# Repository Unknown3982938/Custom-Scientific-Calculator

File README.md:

# Custom-Scientific-Calculator
An open-source custom scientific calculator based on an ESP32, featuring a dedicated keypad matrix, MCP23017 I/O expansion, ST7789 display, rechargeable Li-ion power system, and a custom PCB.

# Project Status
## Work-In-Progress (WIP)
The hardware is currently undergoing PCB and mechanical development. Firmware and enclosure designs are also under active development and may change as physical prototypes are assembled and tested.

# Features
- ESP32-based controller
- ST7789 Color TFT (2.8 inch)
- MCP23017 I/O Expander
- 45 key Physical key matrix (custom)
- SD card support(OPTIONAL)
- Scientific and mathematical functions
- Rechargeable battery
- Modular/Serviceable design (planned to make a compact version, consisting of SMTs instead of THTs)
- Custom PCB
- Custom enclosure

# Repository Contents
- HARDWARE/ - Schematic, BOM, and PCB layout
- FIRMWARE/ - Sketch Code and other software related contents
- CAD/ENCLOSURE/ - Enclosure and Mechanical CAD files
- Manufacturing/ - fabrication-ready manufacturing files
- REFERENCES - Additional materials and information (e.g. Simulations, tests, and additional datas)

# Hardware
The calculator uses a custom PCB designed specifically for the project. The hardware is still being refined and has not yet completed final physical validation.

# Firmware
Firmware development is currently in progress. The included firmware represents the current development state and is subject to change as the hardware is validated.

# CAD
The enclosure and other mechanical components are included as CAD files. These designs are still being refined alongside the PCB and physical prototype.

# Goals
The goal is to create a functional, portable scientific calculator while gaining practical experience in:
- PCB design
- Embedded programming
- Human-machine interfaces
- Power management
- Mechanical design
- Electronics Manufacturing

---

The project is being developed incrementally, with hardware and software tested as each subsystem is completed.

---

# Socials:
(for other projects that is currently independently developed)

- https://tiktok.com/@philie_imation_001 (TIKTOK account)
- (some are set to private for now)

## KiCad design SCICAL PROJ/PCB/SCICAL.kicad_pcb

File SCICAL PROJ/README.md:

# Custom-Scientific-Calculator
A custom-built scientific calculator designed and developed from scratch as a hardware project.

# Features
- ESP32 Based man controller
- Color TFT (2.8 inch)
- Physical key matrix (custom)
- Scientific and mathematical functions
- Rechargeable battery 
- Custom PCB
- Custom enclosure

# Project status
The project is currently in development. The schematic and PCB are being designed, while the firmware and user interface are being developed alongsde the hardware

# Goals
The goal is to create a functional, portable scientific calculator while gaining practical experience in:
- PCB design
- Embedded programmng
- Human-machine interfaces
- Power management
- Mechanical design
- Electronics Manufucturing

---

The project is being developed incrementally, with hardware and software tested as each subsystem is completed.

---

# Code:
(Currently still on queue, it will be set into development once hardware is acquired and finished)

---

# Socials:
(for other projects that is currently independently developed)

- https://tiktok.com/@philie_imation_001 (TIKTOK account)
- (some are set to private for now)

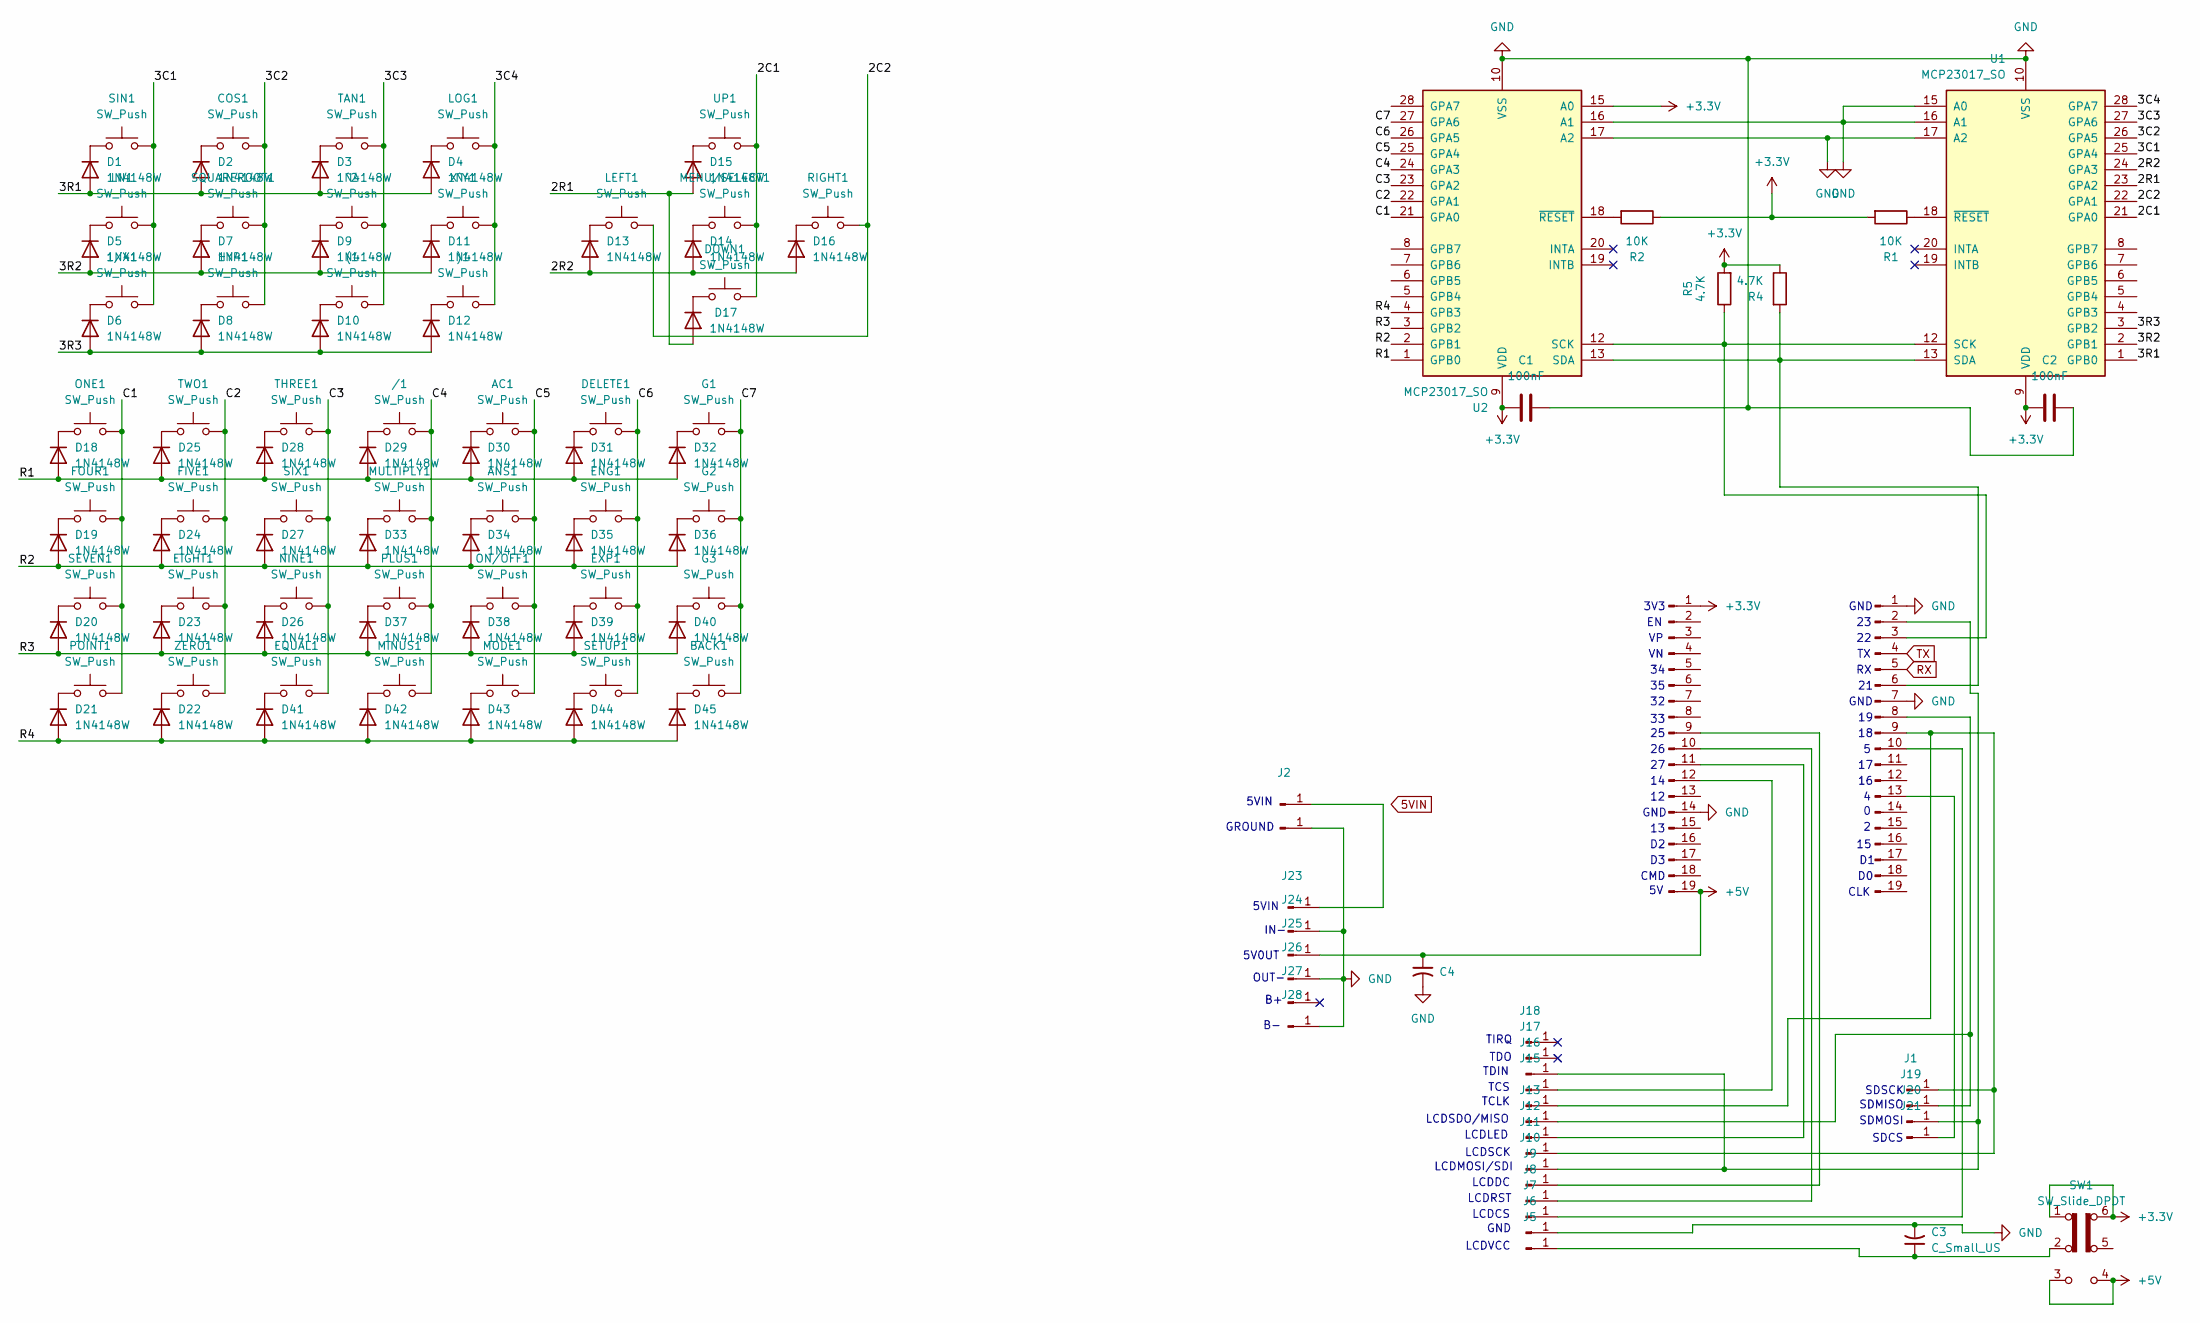
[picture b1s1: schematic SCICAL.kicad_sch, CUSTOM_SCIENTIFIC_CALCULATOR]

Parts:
1/X1: SW_Push; SW_PUSH_6mm
(1: SW_Push; SW_PUSH_6mm
)1: SW_Push; SW_PUSH_6mm
/1: SW_Push; SW_PUSH_6mm
AC1: SW_Push; SW_PUSH_6mm
ANS1: SW_Push; SW_PUSH_6mm
BACK1: SW_Push; SW_PUSH_6mm
C1, C2: 100nF; C_Disc_D3.0mm_W1.6mm_P2.50mm
C3: C_Small_US; C_Radial_D4.0mm_H5.0mm_P1.50mm
C4: C_Small_US; C_Radial_D5.0mm_H11.0mm_P2.00mm
COS1: SW_Push; SW_PUSH_6mm
D1, D2, D3, D4, D5, D6, D7, D8, D9, D10, D11, D12, D13, D14, D15, D16, D17, D18, D19, D20, D21, D22, D23, D24, D25, D26, D27, D28, D29, D30, D31, D32, D33, D34, D35, D36, D37, D38, D39, D40, D41, D42, D43, D44, D45: 1N4148W; D_DO-35_SOD27_P7.62mm_Horizontal
DELETE1: SW_Push; SW_PUSH_6mm
DOWN1: SW_Push; SW_PUSH_6mm
EIGHT1: SW_Push; SW_PUSH_6mm
ENG1: SW_Push; SW_PUSH_6mm
EQUAL1: SW_Push; SW_PUSH_6mm
EXP1: SW_Push; SW_PUSH_6mm
FIVE1: SW_Push; SW_PUSH_6mm
FOUR1: SW_Push; SW_PUSH_6mm
G1, G2, G3: SW_Push; SW_PUSH_6mm
HYP1: SW_Push; SW_PUSH_6mm
J1, J2, J5, J6, J7, J8, J9, J10, J11, J12, J13, J14, J15, J16, J17, J18, J19, J20, J21, J22: Conn_01x01_Pin; SolderWirePad_1x01_SMD_1x2mm
J3, J4: Conn_01x19_Pin; PinHeader_1x19_P2.54mm_Vertical
J23, J24, J25, J26, J27, J28: Conn_01x01_Pin; TestPoint_Pad_2.0x2.0mm
LEFT1: SW_Push; SW_PUSH_6mm
LN1: SW_Push; SW_PUSH_6mm
LOG1: SW_Push; SW_PUSH_6mm
MENU/SELECT1: SW_Push; SW_PUSH_6mm
MINUS1: SW_Push; SW_PUSH_6mm
MODE1: SW_Push; SW_PUSH_6mm
MULTIPLY1: SW_Push; SW_PUSH_6mm
NINE1: SW_Push; SW_PUSH_6mm
ON/OFF1: SW_Push; SW_PUSH_6mm
ONE1: SW_Push; SW_PUSH_6mm
PLUS1: SW_Push; SW_PUSH_6mm
POINT1: SW_Push; SW_PUSH_6mm
R1, R2: 10K; R_Axial_DIN0207_L6.3mm_D2.5mm_P10.16mm_Horizontal
R4, R5: 4.7K; R_Axial_DIN0207_L6.3mm_D2.5mm_P10.16mm_Horizontal
RIGHT1: SW_Push; SW_PUSH_6mm
SETUP1: SW_Push; SW_PUSH_6mm
SEVEN1: SW_Push; SW_PUSH_6mm
SIN1: SW_Push; SW_PUSH_6mm
SIX1: SW_Push; SW_PUSH_6mm
SQUAREROOT1: SW_Push; SW_PUSH_6mm
SW1: SW_Slide_DPDT; SW_CK_JS202011CQN_DPDT_Straight
TAN1: SW_Push; SW_PUSH_6mm
THREE1: SW_Push; SW_PUSH_6mm
TWO1: SW_Push; SW_PUSH_6mm
U1, U2: MCP23017_SO; SOIC-28W_7.5x17.9mm_P1.27mm
UP1: SW_Push; SW_PUSH_6mm
X^Y1: SW_Push; SW_PUSH_6mm
ZERO1: SW_Push; SW_PUSH_6mm
^2: SW_Push; SW_PUSH_6mm

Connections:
+3.3V: C1.1, C2.2, J3.1, R1.2, R2.1, R4.1, R5.2, SW1.1 (A), SW1.6 (C), U1.9 (VDD), U2.9 (VDD), U2.15 (A0)
+5V: C4.1, J3.19, J25.1, SW1.3 (C), SW1.4 (A)
/2C1: DOWN1.2, MENU/SELECT1.2, U1.21 (GPA0), UP1.2
/2C2: LEFT1.2, RIGHT1.2, U1.22 (GPA1)
/2R1: D15.2 (A), D17.2 (A), U1.23 (GPA2)
/2R2: D13.2 (A), D14.2 (A), D16.2 (A), U1.24 (GPA3)
/3C1: 1/X1.2, LN1.2, SIN1.2, U1.25 (GPA4)
/3C2: COS1.2, HYP1.2, SQUAREROOT1.2, U1.26 (GPA5)
/3C3: (1.2, TAN1.2, U1.27 (GPA6), ^2.2
/3C4: )1.2, LOG1.2, U1.28 (GPA7), X^Y1.2
/3R1: D1.2 (A), D2.2 (A), D3.2 (A), D4.2 (A), U1.1 (GPB0)
/3R2: D5.2 (A), D7.2 (A), D9.2 (A), D11.2 (A), U1.2 (GPB1)
/3R3: D6.2 (A), D8.2 (A), D10.2 (A), D12.2 (A), U1.3 (GPB2)
/C1: FOUR1.2, ONE1.2, POINT1.2, SEVEN1.2, U2.21 (GPA0)
/C2: EIGHT1.2, FIVE1.2, TWO1.2, U2.22 (GPA1), ZERO1.2
/C3: EQUAL1.2, NINE1.2, SIX1.2, THREE1.2, U2.23 (GPA2)
/C4: /1.2, MINUS1.2, MULTIPLY1.2, PLUS1.2, U2.24 (GPA3)
/C5: AC1.2, ANS1.2, MODE1.2, ON/OFF1.2, U2.25 (GPA4)
/C6: DELETE1.2, ENG1.2, EXP1.2, SETUP1.2, U2.26 (GPA5)
/C7: BACK1.2, G1.2, G2.2, G3.2, U2.27 (GPA6)
/R1: D18.2 (A), D25.2 (A), D28.2 (A), D29.2 (A), D30.2 (A), D31.2 (A), D32.2 (A), U2.1 (GPB0)
/R2: D19.2 (A), D24.2 (A), D27.2 (A), D33.2 (A), D34.2 (A), D35.2 (A), D36.2 (A), U2.2 (GPB1)
/R3: D20.2 (A), D23.2 (A), D26.2 (A), D37.2 (A), D38.2 (A), D39.2 (A), D40.2 (A), U2.3 (GPB2)
/R4: D21.2 (A), D22.2 (A), D41.2 (A), D42.2 (A), D43.2 (A), D44.2 (A), D45.2 (A), U2.4 (GPB3)
GND: C1.2, C2.1, C3.2, C4.2, J3.14, J4.1, J4.7, J6.1, J22.1, J24.1, J26.1, J28.1, U1.10 (VSS), U1.15 (A0), U1.16 (A1), U1.17 (A2), U2.10 (VSS), U2.16 (A1), U2.17 (A2)
unnamed: D1.1 (K), SIN1.1
unnamed: COS1.1, D2.1 (K)
unnamed: D3.1 (K), TAN1.1
unnamed: D4.1 (K), LOG1.1
unnamed: D5.1 (K), LN1.1
unnamed: 1/X1.1, D6.1 (K)
unnamed: D7.1 (K), SQUAREROOT1.1
unnamed: D8.1 (K), HYP1.1
unnamed: D9.1 (K), ^2.1
unnamed: (1.1, D10.1 (K)
unnamed: D11.1 (K), X^Y1.1
unnamed: )1.1, D12.1 (K)
unnamed: D13.1 (K), LEFT1.1
unnamed: D14.1 (K), MENU/SELECT1.1
unnamed: D15.1 (K), UP1.1
unnamed: D16.1 (K), RIGHT1.1
unnamed: D17.1 (K), DOWN1.1
unnamed: D18.1 (K), ONE1.1
unnamed: D19.1 (K), FOUR1.1
unnamed: D20.1 (K), SEVEN1.1
unnamed: D21.1 (K), POINT1.1
unnamed: D22.1 (K), ZERO1.1
unnamed: D23.1 (K), EIGHT1.1
unnamed: D24.1 (K), FIVE1.1
unnamed: D25.1 (K), TWO1.1
unnamed: D26.1 (K), NINE1.1
unnamed: D27.1 (K), SIX1.1
unnamed: D28.1 (K), THREE1.1
unnamed: /1.1, D29.1 (K)
unnamed: AC1.1, D30.1 (K)
unnamed: D31.1 (K), DELETE1.1
unnamed: D32.1 (K), G1.1
unnamed: D33.1 (K), MULTIPLY1.1
unnamed: ANS1.1, D34.1 (K)
unnamed: D35.1 (K), ENG1.1
unnamed: D36.1 (K), G2.1
unnamed: D37.1 (K), PLUS1.1
unnamed: D38.1 (K), ON/OFF1.1
unnamed: D39.1 (K), EXP1.1
unnamed: D40.1 (K), G3.1
unnamed: D41.1 (K), EQUAL1.1
unnamed: D42.1 (K), MINUS1.1
unnamed: D43.1 (K), MODE1.1
unnamed: D44.1 (K), SETUP1.1
unnamed: BACK1.1, D45.1 (K)
unnamed: J1.1, J4.9, J11.1, J14.1
unnamed: J2.1, J23.1
unnamed: J3.9, J9.1
unnamed: J3.10, J8.1
unnamed: J4.3, R5.1, U1.12 (SCK), U2.12 (SCK)
unnamed: J4.6, R4.2, U1.13 (SDA), U2.13 (SDA)
unnamed: J4.10, J7.1
unnamed: C3.1, J5.1, SW1.2 (B)
unnamed: J4.2, J10.1, J16.1, J20.1
unnamed: J3.11, J12.1
unnamed: J4.8, J13.1, J19.1
unnamed: J3.12, J15.1
unnamed: J4.13, J21.1
unnamed: R1.1, U1.18 (~RESET)
unnamed: R2.2, U2.18 (~RESET)
RX: J4.5
TX: J4.4

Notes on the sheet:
SDCS
5V0UT
TCS
LCDLED
SDSCK
LCDSCK
SDMISO
CMD
SDMOSI
TDO
TCLK
3V3
IN-
LCDMOSI/SDI
LCDCS
LCDSDO/MISO
CLK
GND
OUT-
GROUND
5VIN
LCDDC
LCDVCC
LCDRST
TIRQ
TDIN
5VIN

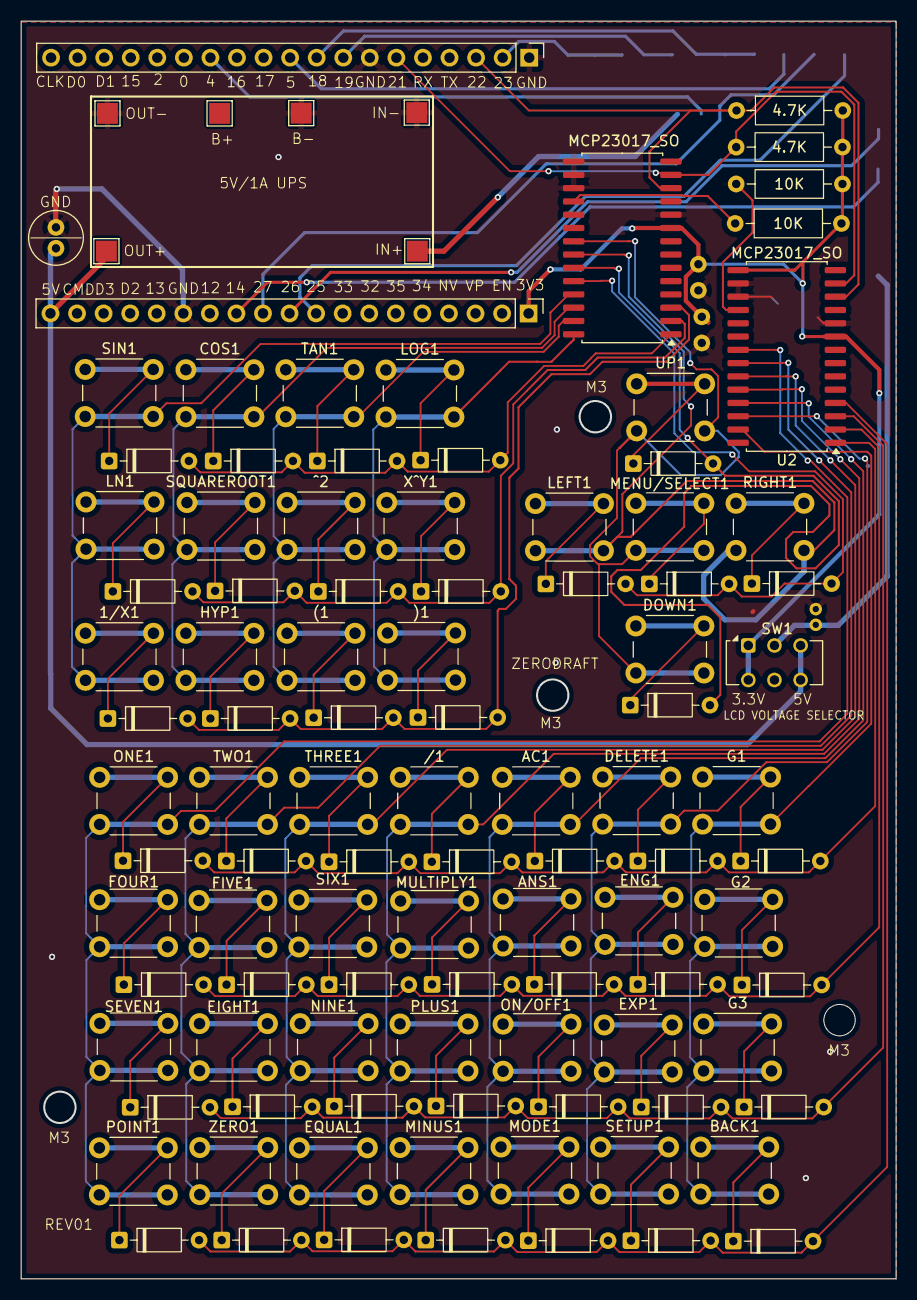
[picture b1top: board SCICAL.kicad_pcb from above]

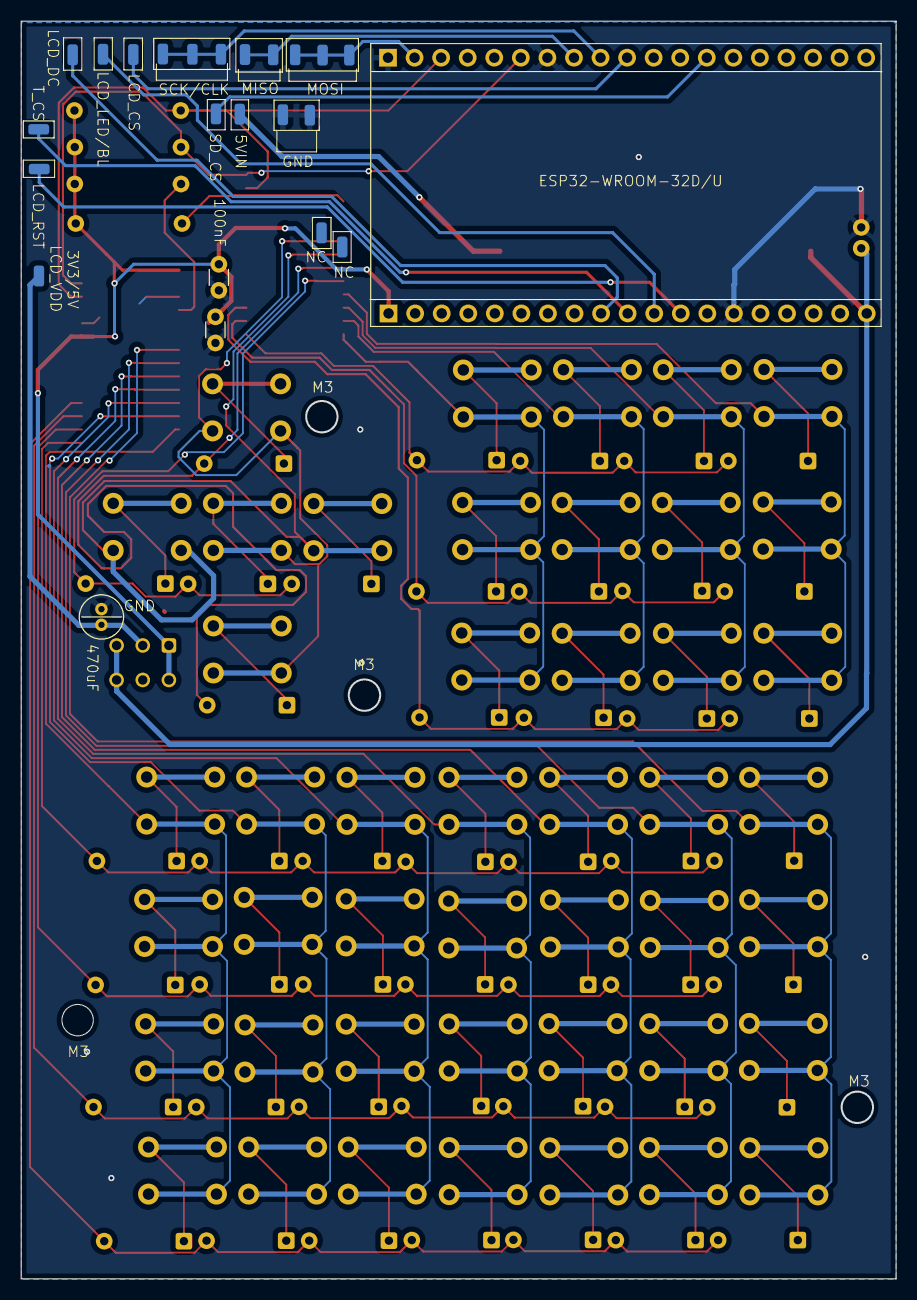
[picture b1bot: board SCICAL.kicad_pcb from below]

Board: 2 copper layers, 83.7 x 120.2 mm, 129 parts (23 on the bottom side), 85 nets.
